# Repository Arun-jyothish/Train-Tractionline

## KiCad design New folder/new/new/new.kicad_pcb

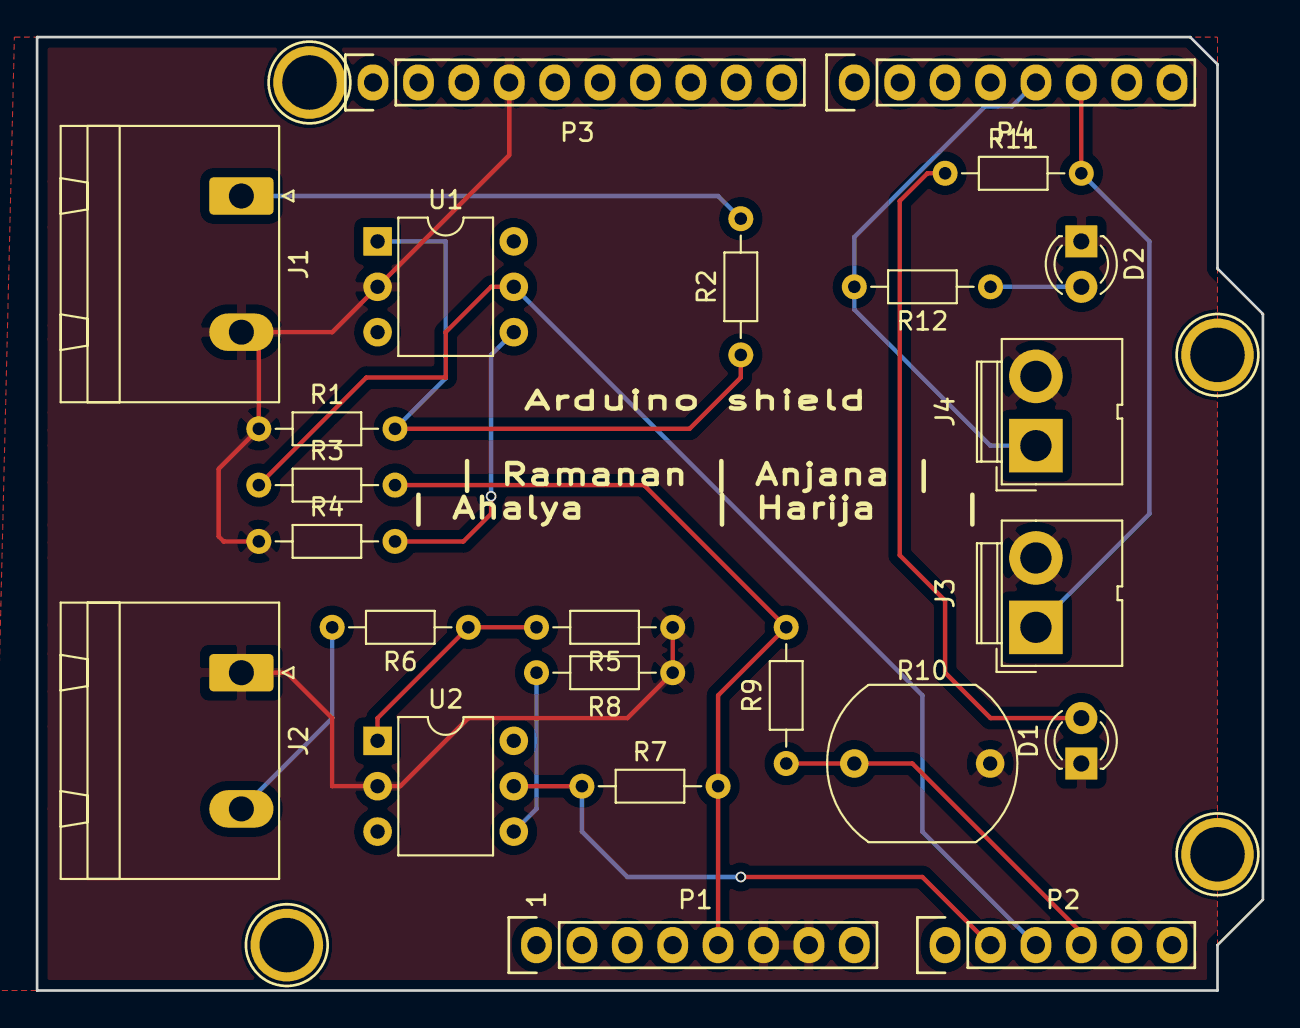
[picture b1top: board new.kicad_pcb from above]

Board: 2 copper layers, 68.6 x 53.3 mm, 28 parts (0 on the bottom side), 17 nets.

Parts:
D1, D2: LED; LED_D3.0mm_FlatTop
J1, J2: Conn_01x02; PhoenixContact_GMSTBA_2,5_2-G-7,62_1x02_P7.62mm_Horizontal
J3, J4: Conn_01x02; JWT_A3963_1x02_P3.96mm_Vertical
P1: Power; Socket_Strip_Arduino_1x08
P2: Analog; Socket_Strip_Arduino_1x06
P3: Digital; Socket_Strip_Arduino_1x10
P4: Digital; Socket_Strip_Arduino_1x08
P5, P6, P7, P8: CONN_01X01; Arduino_1pin
R1, R2, R3, R4, R5, R6, R7, R8, R9, R11, R12: R; R_Axial_DIN0204_L3.6mm_D1.6mm_P7.62mm_Horizontal
R10: LDR03; R_LDR_10x8.5mm_P7.6mm_Vertical
U1, U2: 4N25; DIP-6_W7.62mm

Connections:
+5V: P1.5, R3.2, R7.2, R9.2
/2: J3.1, P4.6, R11.2
/3(**): J4.1, P4.5, R12.2
/A3: P2.4, R9.1, R10.1
/A4(SDA): P2.5, P3.2
/A5(SCL): P2.6, P3.1
GND: D1.1, D2.1, J1.2, J2.1, J3.2, J4.2, P1.6, P1.7, P3.4, R1.1, R4.1, R5.1, R8.1, R10.2, U1.2, U2.2
unnamed: D1.2, R11.1
unnamed: D2.2, R12.1
unnamed: J1.1, R2.2
unnamed: J2.2, R6.2
unnamed: R1.2, R2.1, U1.1
unnamed: R4.2, U1.4
unnamed: R5.2, R6.1, U2.1
unnamed: R8.2, U2.4
input_ref: P2.3, R3.1, U1.5
output_ref: P2.2, R7.1, U2.5

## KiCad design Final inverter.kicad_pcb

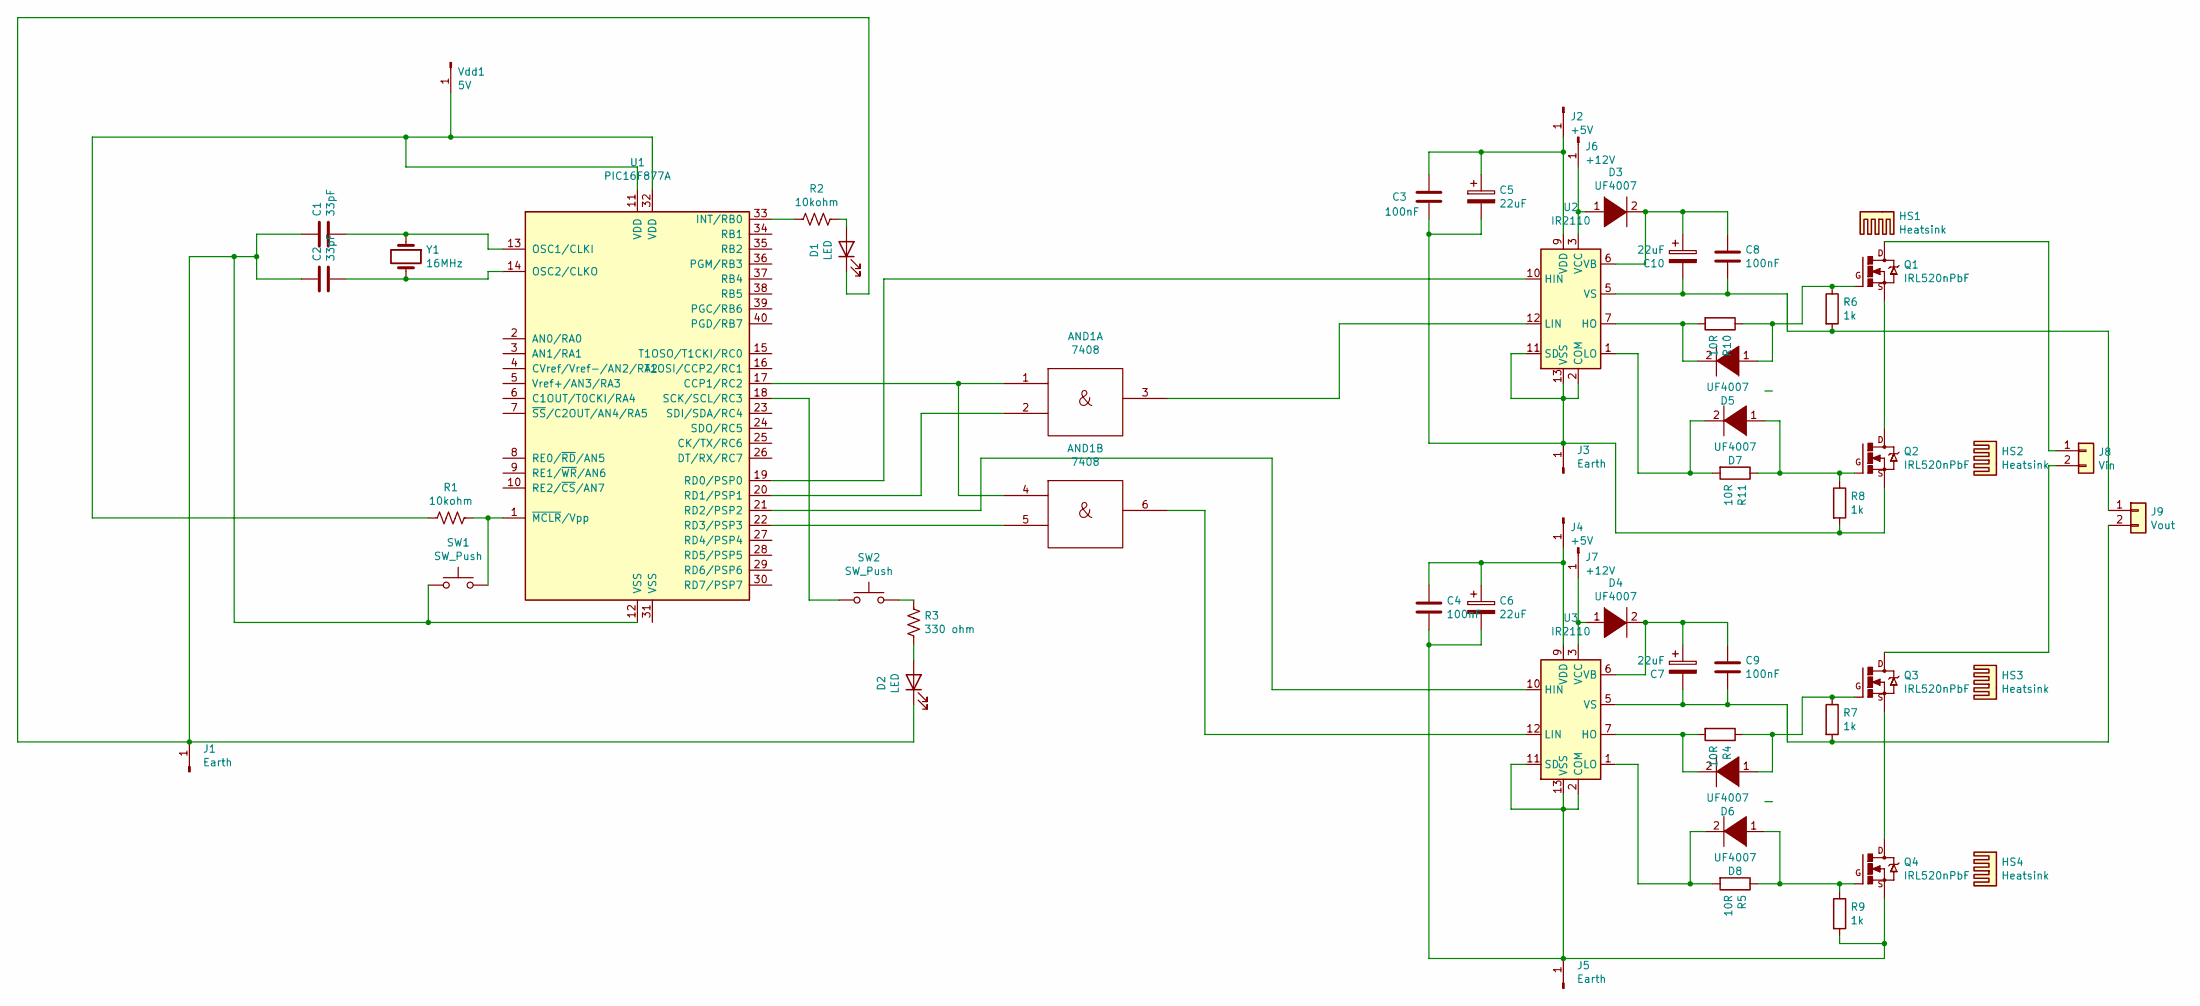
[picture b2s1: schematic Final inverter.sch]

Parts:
AND1: 7408; DIP-14_W10.16mm_LongPads
C1, C2: 33pF; C_Axial_L19.0mm_D7.5mm_P25.00mm_Horizontal
C3, C4: 100nF; C_Axial_L19.0mm_D7.5mm_P25.00mm_Horizontal
C5, C6, C7, C10: 22uF; CP_Axial_L29.0mm_D10.0mm_P35.00mm_Horizontal
C8, C9: 100nF; C_Axial_L12.0mm_D8.5mm_P20.00mm_Horizontal
D1, D2: LED; LED_D3.0mm_Horizontal_O1.27mm_Z2.0mm
D3, D4, D5, D6, D7, D8: UF4007; D_DO-15_P10.16mm_Horizontal
HS1, HS2, HS3, HS4: Heatsink; Heatsink_Stonecold_HS-132_32x14mm_2xFixation1.5mm
J1, J3, J5: Earth; Pin_D1.0mm_L10.0mm
J2, J4: +5V; Pin_D1.3mm_L11.3mm_W2.8mm_Flat
J6, J7: +12V; Pin_D1.3mm_L11.0mm_LooseFit
J8: Vin; JWT_A3963_1x02_P3.96mm_Vertical
J9: Vout; JWT_A3963_1x02_P3.96mm_Vertical
Q1, Q2, Q3, Q4: IRL520nPbF; TO254P469X1042X1967-3P
R1, R2: 10kohm; R_Axial_DIN0414_L11.9mm_D4.5mm_P20.32mm_Horizontal
R3: 330 ohm; R_Axial_DIN0414_L11.9mm_D4.5mm_P15.24mm_Horizontal
R4, R5, R10, R11: 10R; R_Axial_DIN0414_L11.9mm_D4.5mm_P15.24mm_Horizontal
R6, R7, R8, R9: 1k; R_Axial_DIN0414_L11.9mm_D4.5mm_P20.32mm_Horizontal
SW1, SW2: SW_Push; SW_CW_GPTS203211B
U1: PIC16F877A; DIP-40_W25.4mm_Socket_LongPads
U2, U3: IR2110; DIP-14_W7.62mm
Vdd1: 5V; Pin_D1.3mm_L11.3mm_W2.8mm_Flat
Y1: 16MHz; Crystal_HC49-4H_Vertical

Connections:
Gnd: AND1.7 (Gnd)
unnamed: AND1.1, AND1.4, U1.17 (CCP1/RC2)
unnamed: AND1.2, U1.20 (RD1/PSP1)
unnamed: AND1.3, U2.12 (LIN)
unnamed: AND1.5, U1.22 (RD3/PSP3)
unnamed: AND1.6, U3.12 (LIN)
unnamed: C1.1, C2.1, D1.1 (K), D2.1 (K), J1.1, SW1.1, U1.12 (VSS)
unnamed: C1.2, U1.13 (OSC1/CLKI), Y1.1
unnamed: C2.2, U1.14 (OSC2/CLKO), Y1.2
unnamed: C3.1, C5.1, J2.1, U2.9 (VDD)
unnamed: C3.2, C5.2, J3.1, Q2.3, R8.2, U2.2 (COM), U2.11 (SD), U2.13 (VSS)
unnamed: C4.1, C6.1, J4.1, U3.9 (VDD)
unnamed: C4.2, C6.2, J5.1, Q4.3, R9.2, U3.2 (COM), U3.11 (SD), U3.13 (VSS)
unnamed: C7.1, C9.1, D4.2 (A), U3.6 (VB)
unnamed: C7.2, C9.2, J9.2, R7.2, U3.5 (VS)
unnamed: C8.1, C10.1, D3.2 (A), U2.6 (VB)
unnamed: C8.2, C10.2, J9.1, R6.2, U2.5 (VS)
unnamed: D1.2 (A), R2.1
unnamed: D2.2 (A), R3.1
unnamed: D3.1 (K), J6.1, U2.3 (VCC)
unnamed: D4.1 (K), J7.1, U3.3 (VCC)
unnamed: D5.1 (K), Q1.1, R6.1, R10.1
unnamed: D5.2 (A), R10.2, U2.7 (HO)
unnamed: D6.1 (K), Q3.1, R4.1, R7.1
unnamed: D6.2 (A), R4.2, U3.7 (HO)
unnamed: D7.1 (K), Q2.1, R8.1, R11.1
unnamed: D7.2 (A), R11.2, U2.1 (LO)
unnamed: D8.1 (K), Q4.1, R5.1, R9.1
unnamed: D8.2 (A), R5.2, U3.1 (LO)
unnamed: J8.1, Q1.2
unnamed: J8.2, Q3.2
unnamed: Q1.3, Q2.2
unnamed: Q3.3, Q4.2
unnamed: R1.1, SW1.2, U1.1 (~MCLR~/Vpp)
unnamed: R1.2, U1.11 (VDD), U1.32 (VDD), Vdd1.1
unnamed: R2.2, U1.33 (INT/RB0)
unnamed: R3.2, SW2.2
unnamed: SW2.1, U1.18 (SCK/SCL/RC3)
unnamed: U1.19 (RD0/PSP0), U2.10 (HIN)
unnamed: U1.21 (RD2/PSP2), U3.10 (HIN)
Vcc: AND1.14 (Vcc)

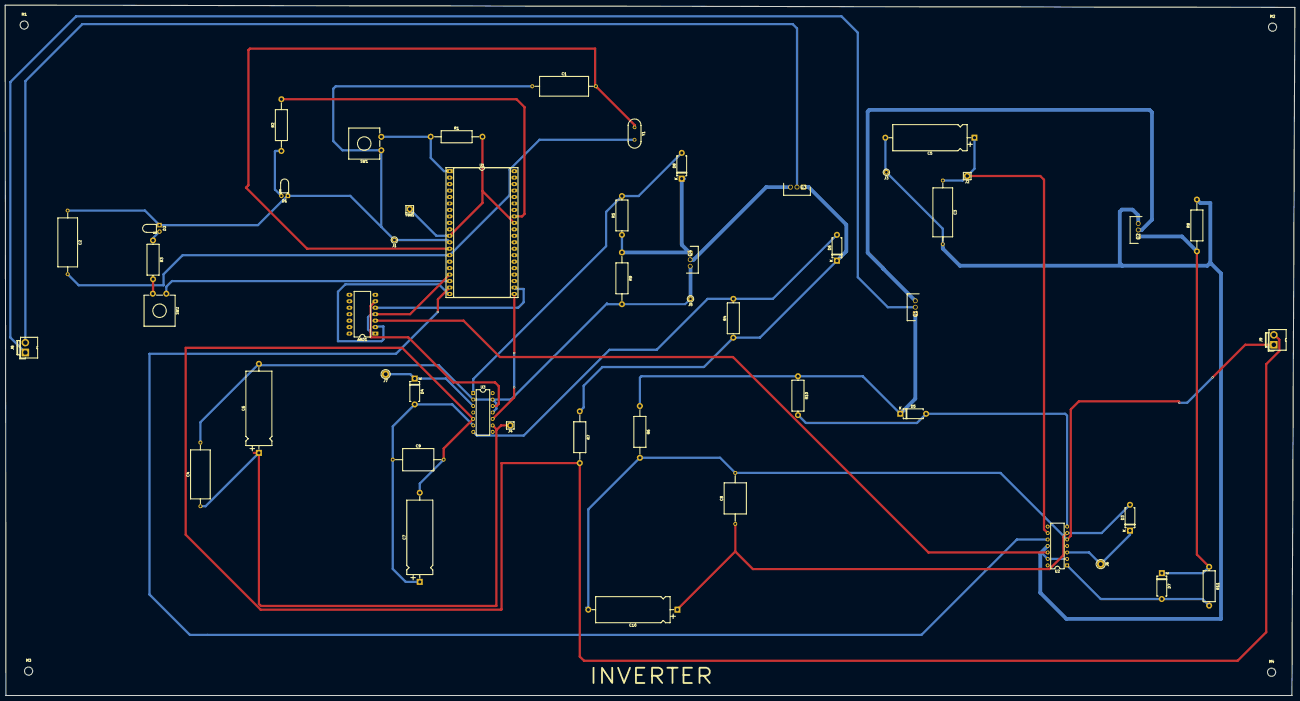
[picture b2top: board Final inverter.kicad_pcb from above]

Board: 2 copper layers, 506.7 x 271.2 mm, 54 parts (0 on the bottom side), 39 nets.

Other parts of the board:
M1, M2, M3, M4: MountingHole_3.2mm_M3

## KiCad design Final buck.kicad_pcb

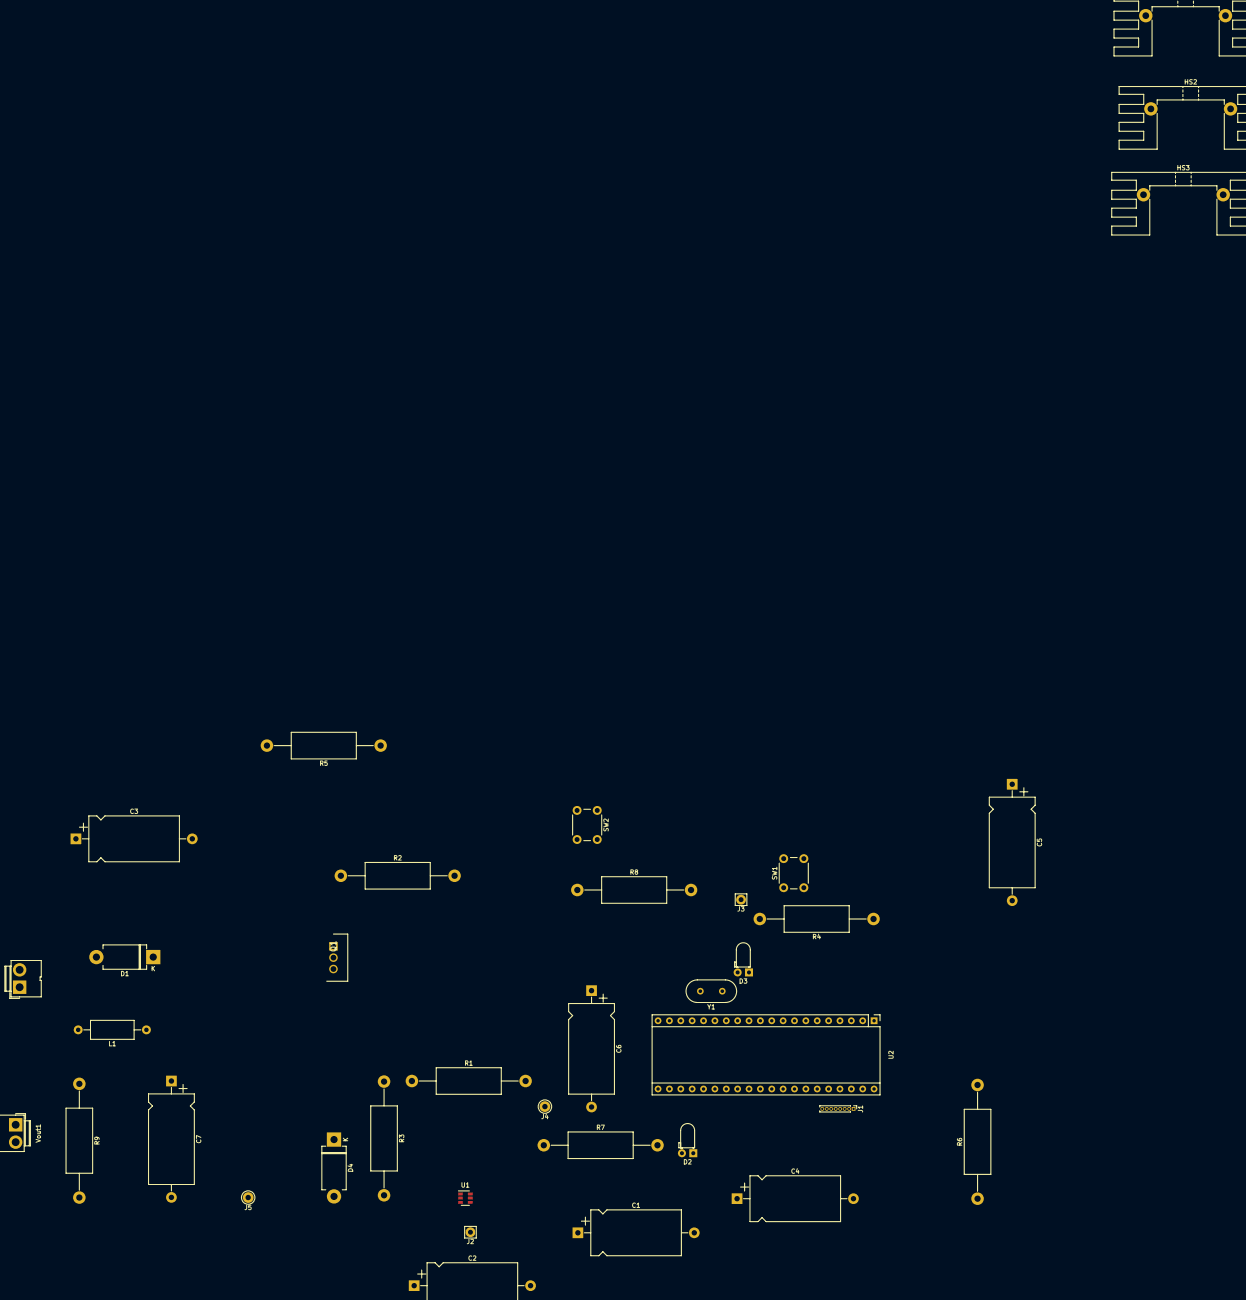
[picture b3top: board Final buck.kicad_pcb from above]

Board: 2 copper layers, 37 parts (0 on the bottom side), 31 nets, no tracks yet.

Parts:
C1: 10uF; CP_Axial_L20.0mm_D10.0mm_P26.00mm_Horizontal
C2, C4: 1nF; CP_Axial_L20.0mm_D10.0mm_P26.00mm_Horizontal
C3: 100pF; CP_Axial_L20.0mm_D10.0mm_P26.00mm_Horizontal
C5, C6: 33pF; CP_Axial_L20.0mm_D10.0mm_P26.00mm_Horizontal
C7: 19.6uF; CP_Axial_L20.0mm_D10.0mm_P26.00mm_Horizontal
D1, D4: MBR1080G; D_DO-201AD_P12.70mm_Horizontal
D2, D3: LED; LED_D3.0mm_Horizontal_O1.27mm_Z6.0mm
HS1, HS2, HS3: Heatsink; Heatsink_Stonecold_HS-132_32x14mm_2xFixation1.5mm
J1: Conn_01x08_Male; PinHeader_1x08_P1.00mm_Vertical
J2: vcc=16V; Pin_D1.1mm_L8.5mm_W2.5mm_FlatFork
J3: vdd=5V; Pin_D1.1mm_L8.5mm_W2.5mm_FlatFork
J4, J5: Earth; Pin_D1.0mm_L10.0mm_LooseFit
L1: 0.2mH; L_Axial_L9.5mm_D4.0mm_P15.24mm_Horizontal_Fastron_SMCC
Q1: IRL520nPbF; TO254P469X1042X1967-3P
R1: 5mohm; R_Axial_DIN0614_L14.3mm_D5.7mm_P25.40mm_Horizontal
R2: 33ohm; R_Axial_DIN0614_L14.3mm_D5.7mm_P25.40mm_Horizontal
R3: 470 ohm; R_Axial_DIN0614_L14.3mm_D5.7mm_P25.40mm_Horizontal
R4, R7: 10kohm; R_Axial_DIN0614_L14.3mm_D5.7mm_P25.40mm_Horizontal
R5: 1kohm; R_Axial_DIN0614_L14.3mm_D5.7mm_P25.40mm_Horizontal
R6: 2Mohm; R_Axial_DIN0614_L14.3mm_D5.7mm_P25.40mm_Horizontal
R8: 330ohm; R_Axial_DIN0614_L14.3mm_D5.7mm_P25.40mm_Horizontal
R9: 2.5ohm; R_Axial_DIN0614_L14.3mm_D5.7mm_P25.40mm_Horizontal
SW1, SW2: SW_Push; SW_PUSH_6mm_H5mm
U1: 1ED44173N01B; SOT-23-6
U2: PIC16F877A; Maple_Mini
Vin1: Conn_01x02; JWT_A3963_1x02_P3.96mm_Vertical
Vout1: Conn_01x02; JWT_A3963_1x02_P3.96mm_Vertical
Y1: 16MHz; Crystal_HC18-U_Vertical

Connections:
unnamed: C1.1, J2.1, U1.4
unnamed: C1.2, C2.2, C3.2, C4.2, C5.1, C6.2, D2.1, D3.1, J4.1, SW1.1, U2.12, U2.31
unnamed: C2.1, R3.2, U1.1
unnamed: C3.1, R5.2, U1.6
unnamed: C4.1, R6.1, U1.5, U2.28
unnamed: C5.2, U2.13, Y1.1
unnamed: C6.1, U2.14, Y1.2
unnamed: C7.1, L1.2, R9.1, Vout1.1
unnamed: C7.2, D4.2, J5.1, R1.2, R9.2, U1.2, Vout1.2
unnamed: D1.1, Q1.2
unnamed: D1.2, Vin1.2
unnamed: D2.2, R7.1
unnamed: D3.2, R8.2
unnamed: D4.1, L1.1, Q1.3
unnamed: J1.1, U2.40
unnamed: J1.2, U2.39
unnamed: J1.3, U2.38
unnamed: J1.4, U2.37
unnamed: J1.5, U2.36
unnamed: J1.6, U2.35
unnamed: J1.7, U2.34
unnamed: J1.8, U2.33
unnamed: J3.1, R4.2, R6.2, U2.11, U2.32
unnamed: Q1.1, R2.1
unnamed: R1.1, R3.1, Vin1.1
unnamed: R2.2, U1.3
unnamed: R4.1, SW1.2, U2.1
unnamed: R5.1, U2.27
unnamed: R7.2, U2.21
unnamed: R8.1, SW2.2
unnamed: SW2.1, U2.18

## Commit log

2021-06-04 'first'
2021-06-04 hello
2021-06-05 compile ok
2021-06-09 first-rough-work
    arduino_shield,3d_board,Silkscreen names, 3d render image,schematics pdf, boost converter-'workon',no-inverter
